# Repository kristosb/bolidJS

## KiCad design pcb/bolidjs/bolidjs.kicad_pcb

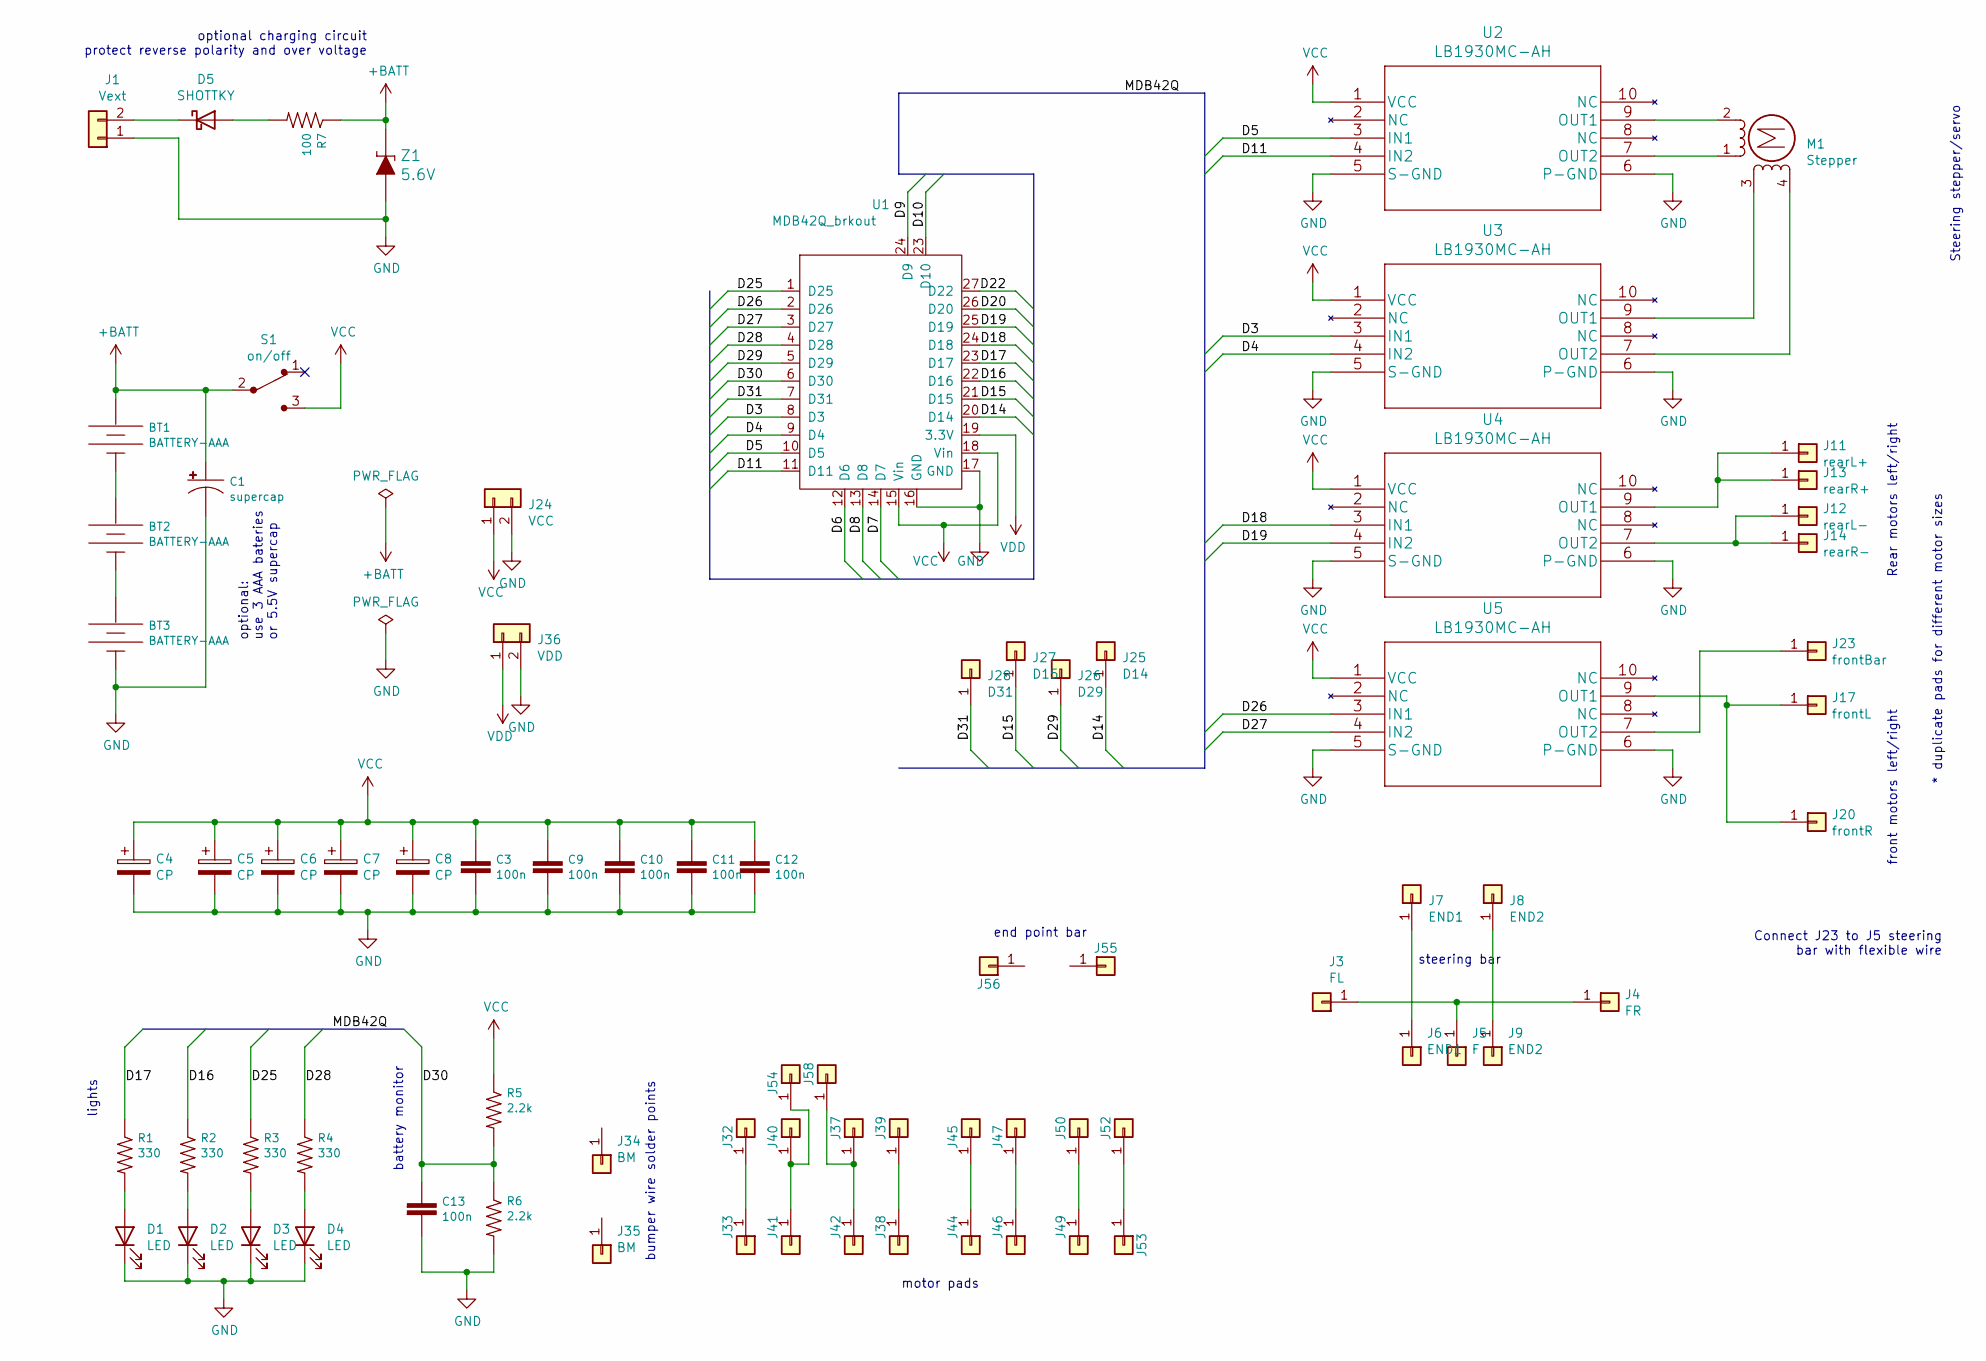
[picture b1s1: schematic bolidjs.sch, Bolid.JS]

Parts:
BT1, BT2, BT3: BATTERY-AAA; BatterySlot_AAA
C1: supercap; super_cap
C3, C9, C10, C11, C12, C13: 100n; 0805
C4, C5, C6, C7, C8: CP; CP_Radial_D5.0mm_P2.50mm
D1, D2, D3, D4: LED; LED_D1.8mm_W1.8mm_H2.4mm_Horizontal_O1.27mm_Z4.9mm
D5: SHOTTKY; Schottkey_D_5W_P10.16mm_Horizontal
J1: Vext; PinHeader_1x02_P2.54mm_Vertical
J3, J32, J33, J37, J38, J39, J40, J41, J42, J44, J45, J46, J47, J49, J50, J52, J53, J54, J55, J56, J58: FL; PinHeader_1x01_P2.54mm_Vertical
J4: FR; PinHeader_1x01_P2.54mm_Vertical
J5: F; PinHeader_1x01_P2.54mm_Vertical
J6, J7: END1; PinHeader_1x01_P2.54mm_Vertical
J8, J9: END2; PinHeader_1x01_P2.54mm_Vertical
J11: rearL+; PinHeader_1x01_P2.54mm_Vertical
J12: rearL-; PinHeader_1x01_P2.54mm_Vertical
J13: rearR+; PinHeader_1x01_P2.54mm_Vertical
J14: rearR-; PinHeader_1x01_P2.54mm_Vertical
J17: frontL; PinHeader_1x01_P2.54mm_Vertical
J20: frontR; PinHeader_1x01_P2.54mm_Vertical
J23: frontBar; PinHeader_1x01_P2.54mm_Vertical
J24: VCC; PinHeader_1x02_P2.54mm_Vertical
J25: D14; PinHeader_1x01_P2.54mm_Vertical
J26: D29; PinHeader_1x01_P2.54mm_Vertical
J27: D15; PinHeader_1x01_P2.54mm_Vertical
J28: D31; PinHeader_1x01_P2.54mm_Vertical
J34, J35: BM; PinHeader_1x01_P2.54mm_Vertical
J36: VDD; PinHeader_1x02_P2.54mm_Vertical
M1: Stepper; screwSliderStepper
R1, R2, R3, R4: 330; 0805
R5, R6: 2.2k; 0805
R7: 100; 0805
S1: on/off; PinHeader_1x03_P2.54mm_Vertical; MPN ATE1D-2M3-10-Z; Digi-Key_PN 563-1157-ND
U1: MDB42Q_brkout; MDBQ42Q_brkout
U2, U3, U4, U5: LB1930MC-AH
Z1: 5.6V; zener_D_5W_P10.16mm_Horizontal; MPN 1N5231BTR; Digi-Key_PN 1N5231BFSCT-ND

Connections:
+BATT: BT1.PWR@ (+), C1.+, R7.1, S1.2 (Com), Z1.K
/D3: U1.8 (D3), U3.3 (IN1)
/D4: U1.9 (D4), U3.4 (IN2)
/D5: U1.10 (D5), U2.3 (IN1)
/D6: U1.12 (D6)
/D7: U1.14 (D7)
/D8: U1.13 (D8)
/D11: U1.11 (D11), U2.4 (IN2)
/D14: J25.1, U1.20 (D14)
/D15: J27.1, U1.21 (D15)
/D16: R2.1, U1.22 (D16)
/D19: U1.25 (D19), U4.4 (IN2)
/D20: U1.26 (D20)
/D22: U1.27 (D22)
/D25: R3.1, U1.1 (D25)
/D26: U1.2 (D26), U5.3 (IN1)
/D27: U1.3 (D27), U5.4 (IN2)
/D28: R4.1, U1.4 (D28)
/D29: J26.1, U1.5 (D29)
/D30: C13.1, R5.2, R6.1, U1.6 (D30)
/D31: J28.1, U1.7 (D31)
GND: BT3.GND@ (-), C1.-, C3.2, C4.2, C5.2, C6.2, C7.2, C8.2, C9.2, C10.2, C11.2, C12.2, C13.2, D1.1 (K), D2.1 (K), D3.1 (K), D4.1 (K), J1.1, J24.2, J36.2, R6.2, U1.16 (GND), U1.17 (GND), U2.5 (S-GND), U2.6 (P-GND), U3.5 (S-GND), U3.6 (P-GND), U4.5 (S-GND), U4.6 (P-GND), U5.5 (S-GND), U5.6 (P-GND), Z1.A
unnamed: BT1.GND@ (-), BT2.PWR@ (+)
unnamed: BT2.GND@ (-), BT3.PWR@ (+)
unnamed: D1.2 (A), R1.2
unnamed: D2.2 (A), R2.2
unnamed: D3.2 (A), R3.2
unnamed: D4.2 (A), R4.2
unnamed: D5.1 (K), J1.2
unnamed: D5.2 (A), R7.2
unnamed: J3.1, J4.1, J5.1
unnamed: J6.1, J7.1
unnamed: J8.1, J9.1
unnamed: J11.1, J13.1, U4.9 (OUT1)
unnamed: J12.1, J14.1, U4.7 (OUT2)
unnamed: J17.1, J20.1, U5.9 (OUT1)
unnamed: J23.1, U5.7 (OUT2)
unnamed: J32.1, J33.1
unnamed: J37.1, J42.1, J58.1
unnamed: J38.1, J39.1
unnamed: J40.1, J41.1, J54.1
unnamed: J44.1, J45.1
unnamed: J46.1, J47.1
unnamed: J49.1, J50.1
unnamed: J52.1, J53.1
unnamed: M1.1, U2.7 (OUT2)
unnamed: M1.2 (-), U2.9 (OUT1)
unnamed: M1.3, U3.9 (OUT1)
unnamed: M1.4, U3.7 (OUT2)
VCC: C3.1, C4.1, C5.1, C6.1, C7.1, C8.1, C9.1, C10.1, C11.1, C12.1, J24.1, R5.1, S1.3, U1.15 (Vin), U1.18 (Vin), U2.1 (VCC), U3.1 (VCC), U4.1 (VCC), U5.1 (VCC)
VDD: J36.1, U1.19 (3.3V)

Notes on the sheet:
Steering stepper/servo
Rear motors left/right
front motors left/right
steering bar
Connect J23 to J5 steering bar with flexible wire
optional charging circuit protect reverse polarity and over voltage
lights
battery monitor
optional: use 3 AAA bateries or 5.5V supercap
bumper wire solder points
* duplicate pads for different motor sizes
motor pads
end point bar

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
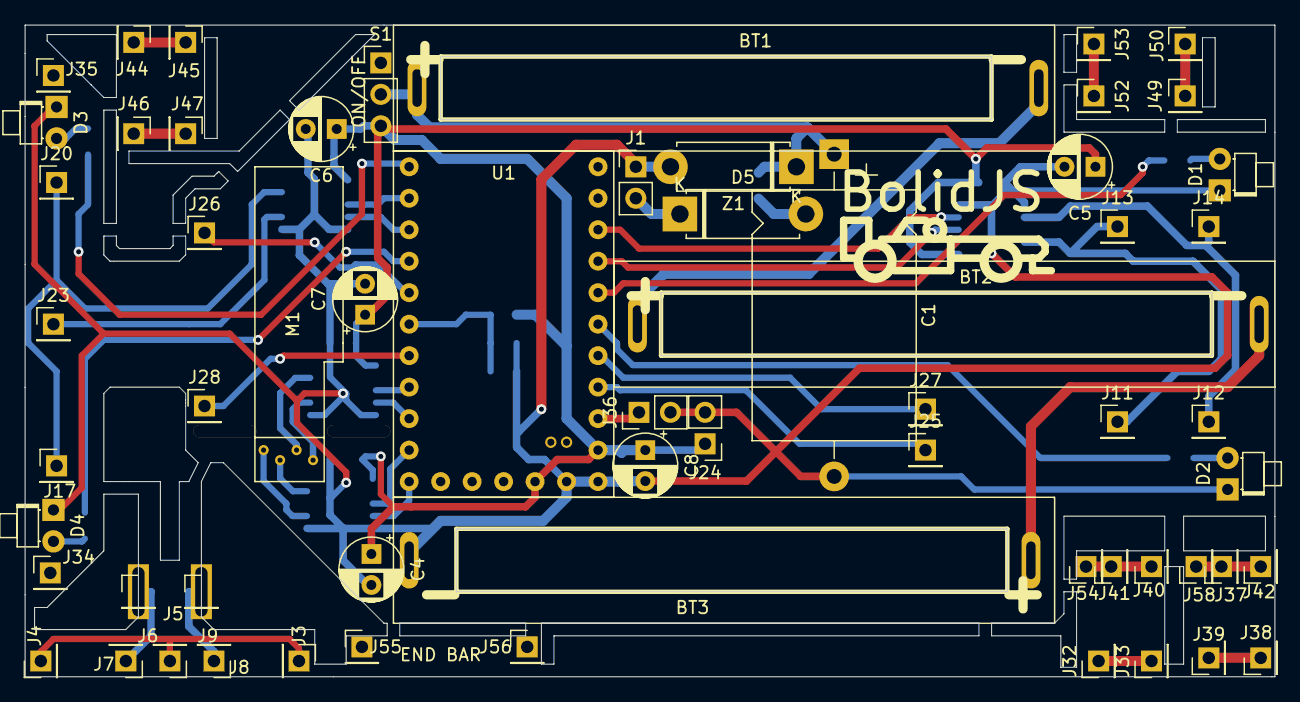
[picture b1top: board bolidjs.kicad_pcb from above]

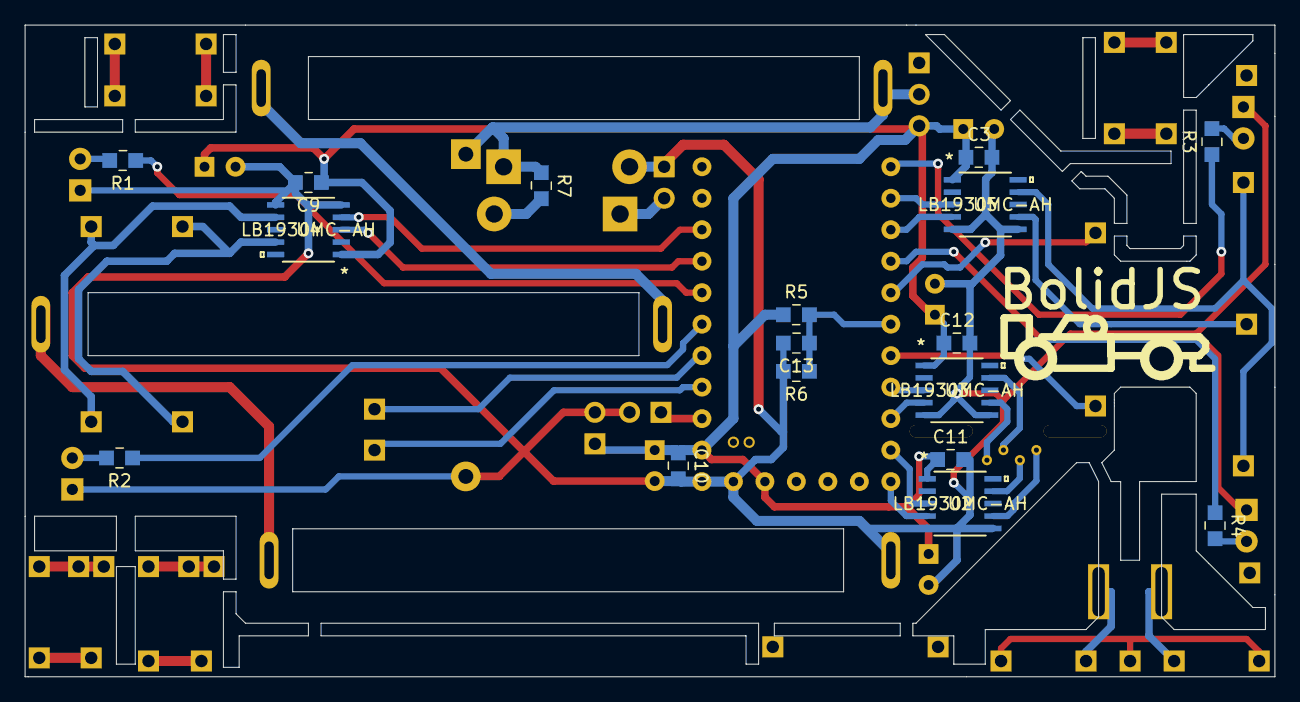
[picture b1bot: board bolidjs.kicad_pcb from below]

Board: 2 copper layers, 100.8 x 52.6 mm, 78 parts (17 on the bottom side), 48 nets.

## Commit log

2020-10-21 adding pdf for schematic and layout
2020-10-21 adding components docs
2020-10-21 steering pic
2020-10-26 added steering option and wheel pads
2020-10-29 removed options for motor sizes
2020-10-29 steering bar is ticker
2020-11-02 minor change
2020-11-03 gerber format
2021-02-08 added bt communication
2021-02-09 calibration routine experiments
2021-02-17 added offset for steering
2021-02-19 break handling
2021-02-19 added breaking motors through fast decay
2021-02-23 heartbeat flashing diodes on disconnect

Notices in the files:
parts and their libraries:
Copyright 2016 Accelerated Designs. All rights reserved.
